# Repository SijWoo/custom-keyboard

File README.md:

# custom-keyboard
Holds the electronic pcb files and src code for my custom keyboard

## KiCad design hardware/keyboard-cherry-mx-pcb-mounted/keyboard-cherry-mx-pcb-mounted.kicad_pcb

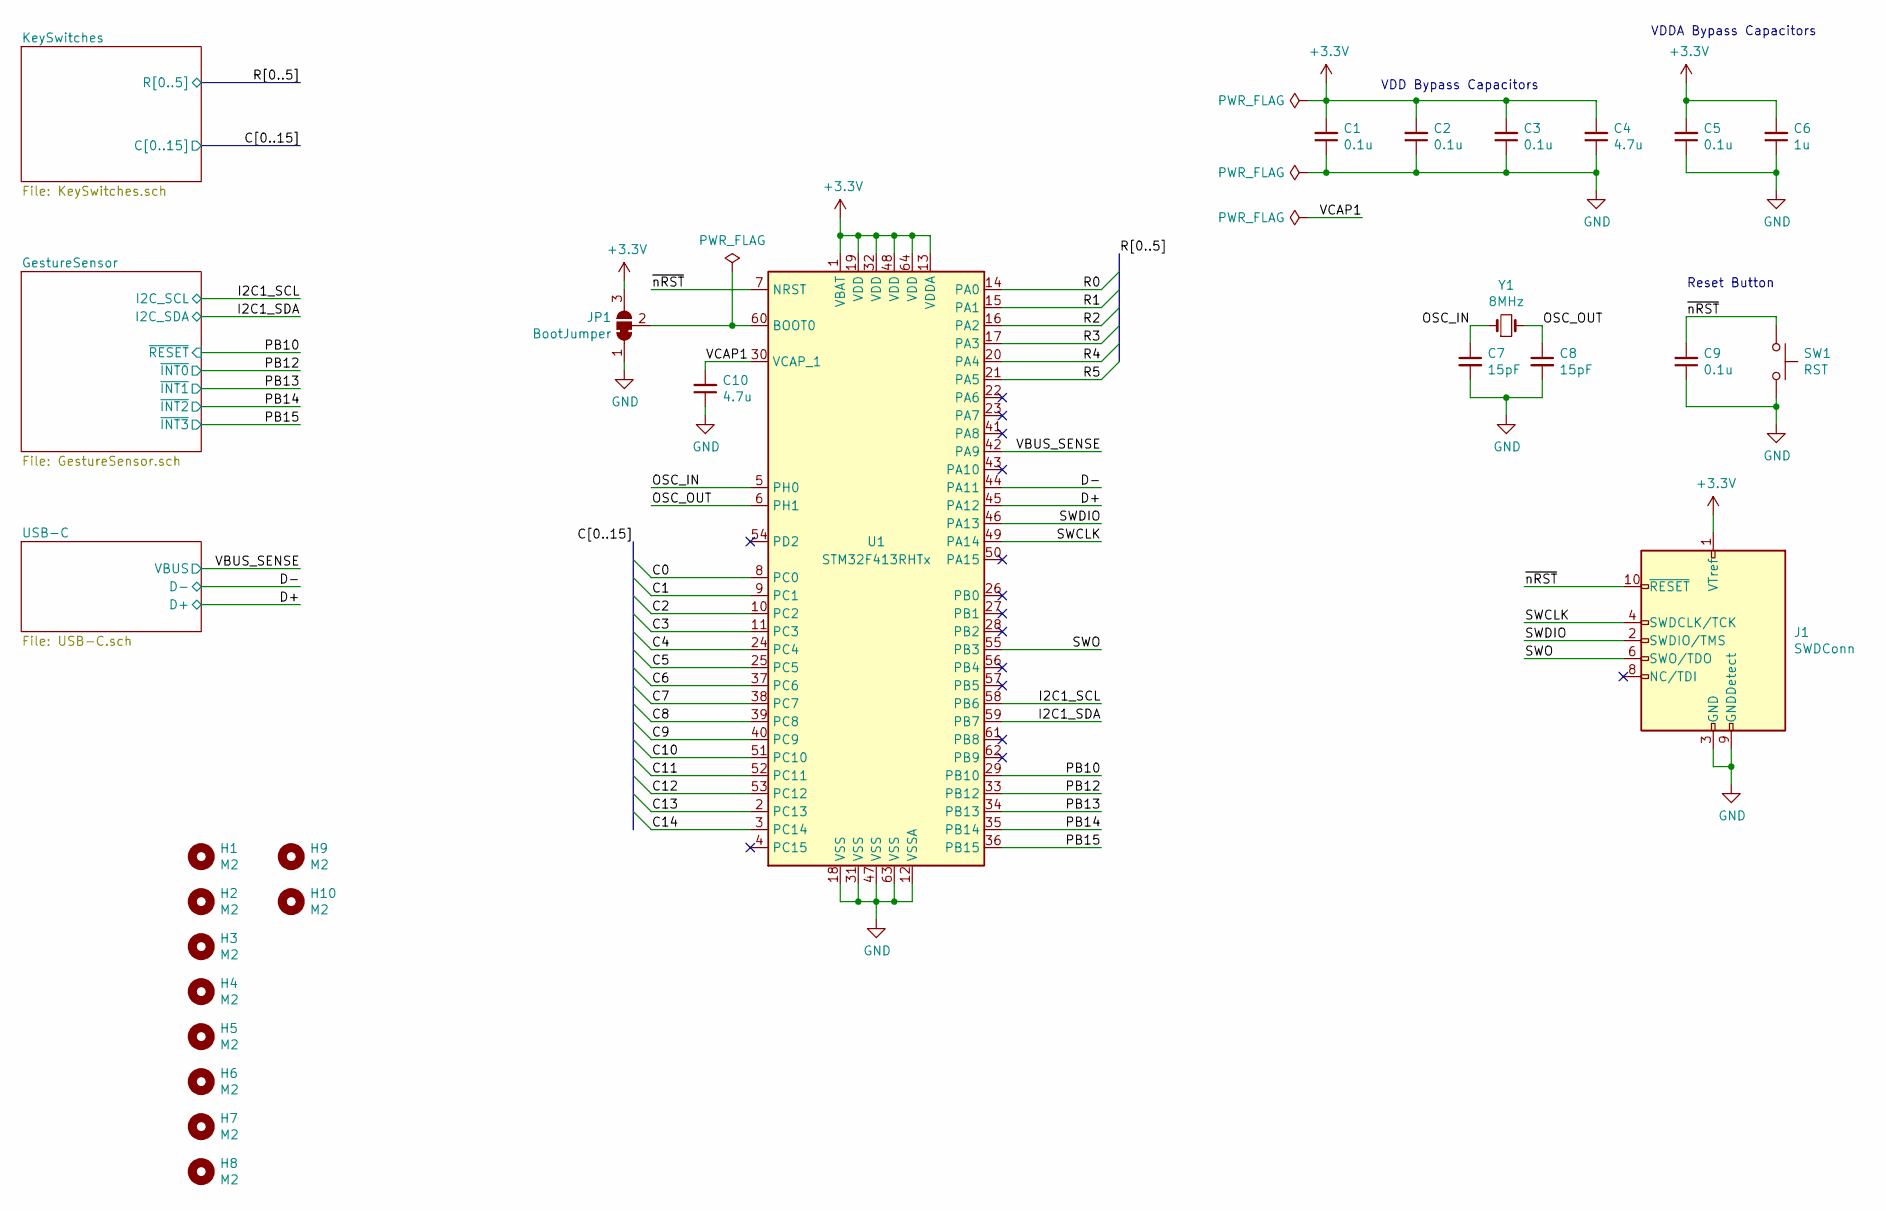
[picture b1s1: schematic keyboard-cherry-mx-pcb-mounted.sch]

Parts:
C1, C2, C3, C5: 0.1u; C_0603_1608Metric
C4, C10: 4.7u; C_0603_1608Metric
C6: 1u; C_0603_1608Metric
C7, C8: 15pF; C_0603_1608Metric
C9: 0.1u; C_0805_2012Metric
H1, H2, H3, H4, H5, H6, H7, H8, H9, H10: M2; MountingHole_2.2mm_M2
J1: SWDConn; Tag-Connect_TC2050-IDC-NL_2x05_P1.27mm_Vertical
JP1: BootJumper; SolderJumper-3_P1.3mm_Bridged12_Pad1.0x1.5mm
SW1: RST; SW_SPST_B3U-1000P
U1: STM32F413RHTx; LQFP-64_10x10mm_P0.5mm
Y1: 8MHz; Crystal_SMD_TXC_7A-2Pin_5x3.2mm

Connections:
+3V3: C1.2, C2.2, C3.2, C4.2, C5.2, C6.2, J1.1 (VTref), JP1.3 (B), U1.1 (VBAT), U1.13 (VDDA), U1.19 (VDD), U1.32 (VDD), U1.48 (VDD), U1.64 (VDD); also elsewhere on the board
+5V: U1.42 (PA9); also elsewhere on the board
/C0: U1.8 (PC0); also elsewhere on the board
/C1: U1.9 (PC1); also elsewhere on the board
/C2: U1.10 (PC2); also elsewhere on the board
/C3: U1.11 (PC3); also elsewhere on the board
/C4: U1.24 (PC4); also elsewhere on the board
/C5: U1.25 (PC5); also elsewhere on the board
/C6: U1.37 (PC6); also elsewhere on the board
/C7: U1.38 (PC7); also elsewhere on the board
/C8: U1.39 (PC8); also elsewhere on the board
/C9: U1.40 (PC9); also elsewhere on the board
/C10: U1.51 (PC10); also elsewhere on the board
/C11: U1.52 (PC11); also elsewhere on the board
/C12: U1.53 (PC12); also elsewhere on the board
/C13: U1.2 (PC13); also elsewhere on the board
/C14: U1.3 (PC14); also elsewhere on the board
/D+: U1.45 (PA12); also elsewhere on the board
/D-: U1.44 (PA11); also elsewhere on the board
/I2C1_SCL: U1.58 (PB6); also elsewhere on the board
/I2C1_SDA: U1.59 (PB7); also elsewhere on the board
/OSC_IN: C7.1, U1.5 (PH0), Y1.1
/OSC_OUT: C8.1, U1.6 (PH1), Y1.2
/PB10: U1.29 (PB10); also elsewhere on the board
/PB12: U1.33 (PB12); also elsewhere on the board
/PB13: U1.34 (PB13); also elsewhere on the board
/PB14: U1.35 (PB14); also elsewhere on the board
/PB15: U1.36 (PB15); also elsewhere on the board
/R0: U1.14 (PA0); also elsewhere on the board
/R1: U1.15 (PA1); also elsewhere on the board
/R2: U1.16 (PA2); also elsewhere on the board
/R3: U1.17 (PA3); also elsewhere on the board
/R4: U1.20 (PA4); also elsewhere on the board
/R5: U1.21 (PA5); also elsewhere on the board
/SWCLK: J1.4 (SWDCLK/TCK), U1.49 (PA14)
/SWDIO: J1.2 (SWDIO/TMS), U1.46 (PA13)
/SWO: J1.6 (SWO/TDO), U1.55 (PB3)
/VCAP1: C10.2, U1.30 (VCAP_1)
/~nRST: C9.2, J1.10 (~RESET~), SW1.1, U1.7 (NRST)
GND: C1.1, C2.1, C3.1, C4.1, C5.1, C6.1, C7.2, C8.2, C9.1, C10.1, J1.3 (GND), J1.5 (GND), J1.9 (GNDDetect), JP1.1 (A), SW1.2, U1.12 (VSSA), U1.18 (VSS), U1.31 (VSS), U1.47 (VSS), U1.63 (VSS); also elsewhere on the board
unnamed: JP1.2 (C), U1.60 (BOOT0)

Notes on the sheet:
VDDA Bypass Capacitors
Reset Button
VDD Bypass Capacitors

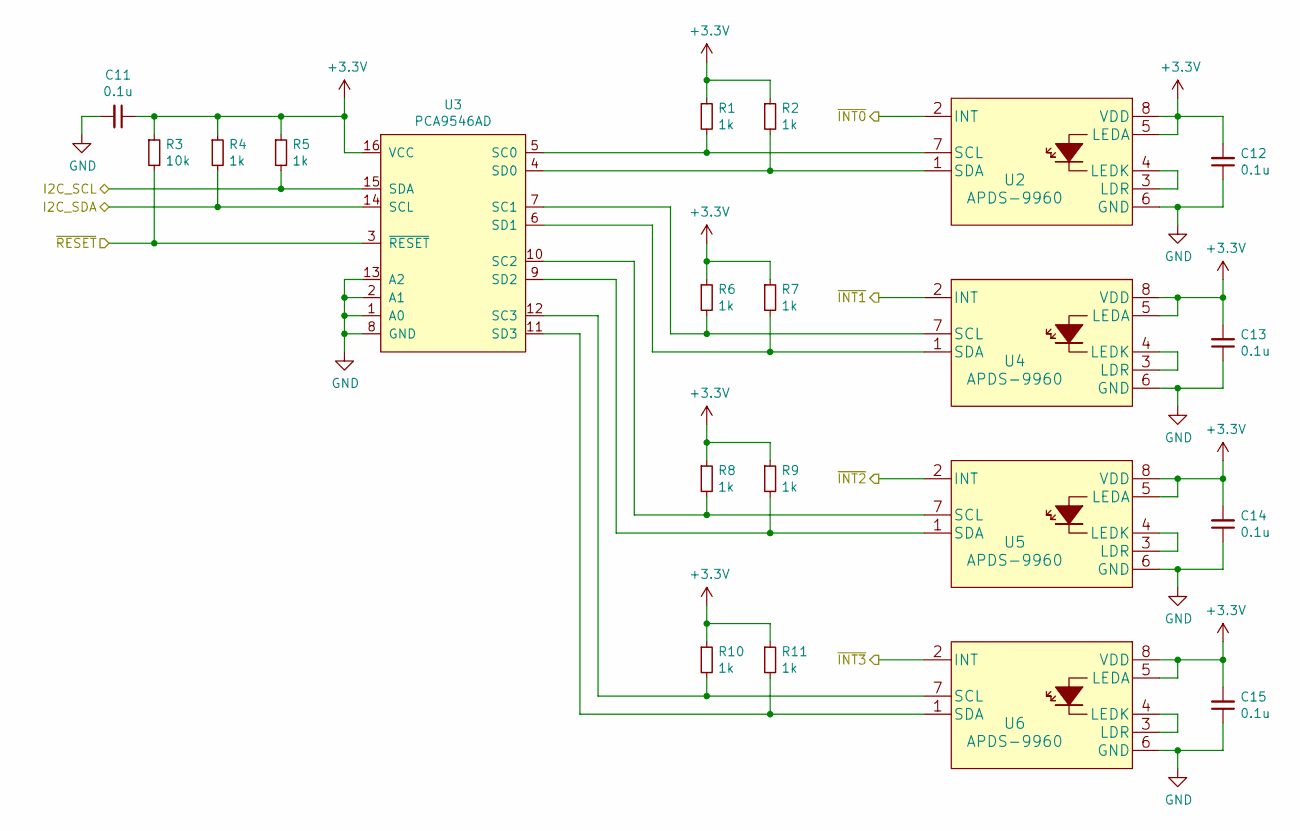
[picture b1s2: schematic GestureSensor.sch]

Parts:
C11, C12, C13, C14, C15: 0.1u; C_0805_2012Metric
R1, R2, R4, R5, R6, R7, R8, R9, R10, R11: 1k; R_0805_2012Metric
R3: 10k; R_0805_2012Metric
U2, U4, U5, U6: APDS-9960; APDS-9930
U3: PCA9546AD; SOIC-16_3.9x9.9mm_P1.27mm

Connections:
+3V3: C11.1, C12.2, C13.2, C14.2, C15.2, R1.1, R2.1, R3.1, R4.1, R5.1, R6.1, R7.1, R8.1, R9.1, R10.1, R11.1, U2.5 (LEDA), U2.8 (VDD), U3.16 (VCC), U4.5 (LEDA), U4.8 (VDD), U5.5 (LEDA), U5.8 (VDD), U6.5 (LEDA), U6.8 (VDD); also elsewhere on the board
/I2C1_SCL: R5.2, U3.15 (SDA); also elsewhere on the board
/I2C1_SDA: R4.2, U3.14 (SCL); also elsewhere on the board
/PB10: R3.2, U3.3 (~RESET); also elsewhere on the board
/PB12: U2.2 (INT); also elsewhere on the board
/PB13: U4.2 (INT); also elsewhere on the board
/PB14: U5.2 (INT); also elsewhere on the board
/PB15: U6.2 (INT); also elsewhere on the board
GND: C11.2, C12.1, C13.1, C14.1, C15.1, U2.6 (GND), U3.1 (A0), U3.2 (A1), U3.8 (GND), U3.13 (A2), U4.6 (GND), U5.6 (GND), U6.6 (GND); also elsewhere on the board
unnamed: R1.2, U2.7 (SCL), U3.5 (SC0)
unnamed: R2.2, U2.1 (SDA), U3.4 (SD0)
unnamed: R6.2, U3.7 (SC1), U4.7 (SCL)
unnamed: R7.2, U3.6 (SD1), U4.1 (SDA)
unnamed: R8.2, U3.10 (SC2), U5.7 (SCL)
unnamed: R9.2, U3.9 (SD2), U5.1 (SDA)
unnamed: R10.2, U3.12 (SC3), U6.7 (SCL)
unnamed: R11.2, U3.11 (SD3), U6.1 (SDA)
unnamed: U2.3 (LDR), U2.4 (LEDK)
unnamed: U4.3 (LDR), U4.4 (LEDK)
unnamed: U5.3 (LDR), U5.4 (LEDK)
unnamed: U6.3 (LDR), U6.4 (LEDK)

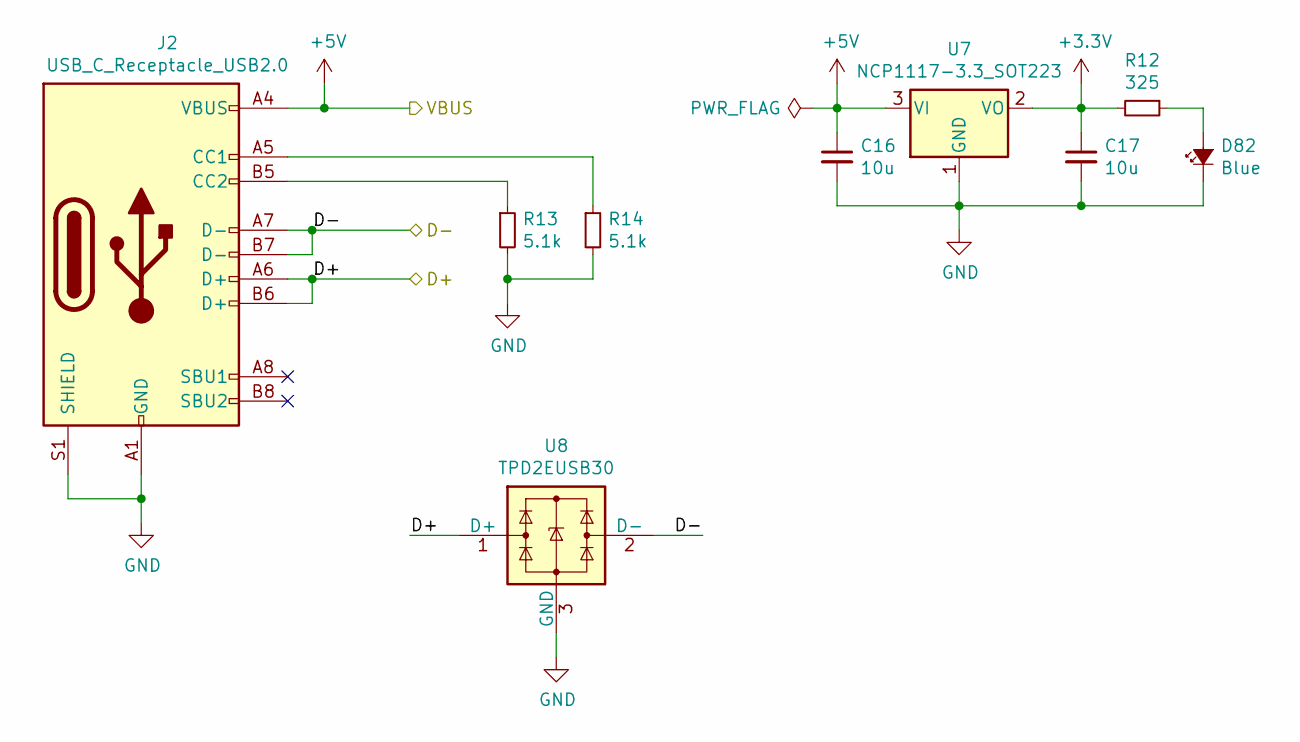
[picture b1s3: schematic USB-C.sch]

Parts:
C16, C17: 10u; C_0805_2012Metric
D82: Blue; LED_0805_2012Metric
J2: USB_C_Receptacle_USB2.0; USB_C_Receptacle_Wurth_632723100021
R12: 325; R_0805_2012Metric
R13, R14: 5.1k; R_0805_2012Metric
U7: NCP1117-3.3_SOT223; SOT-223-3_TabPin2
U8: TPD2EUSB30; Texas_DRT-3

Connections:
+3V3: C17.1, R12.2, U7.2 (VO); also elsewhere on the board
+5V: C16.1, J2.A4 (VBUS), J2.A9 (VBUS), J2.B4 (VBUS), J2.B9 (VBUS), U7.3 (VI); also elsewhere on the board
/D+: J2.A6 (D+), J2.B6 (D+), U8.1 (D+); also elsewhere on the board
/D-: J2.A7 (D-), J2.B7 (D-), U8.2 (D-); also elsewhere on the board
GND: C16.2, C17.2, D82.1 (K), J2.A1 (GND), J2.A12 (GND), J2.B1 (GND), J2.B12 (GND), J2.S1 (SHIELD), R13.2, R14.2, U7.1 (GND), U8.3 (GND); also elsewhere on the board
unnamed: D82.2 (A), R12.1
unnamed: J2.A5 (CC1), R14.1
unnamed: J2.B5 (CC2), R13.1

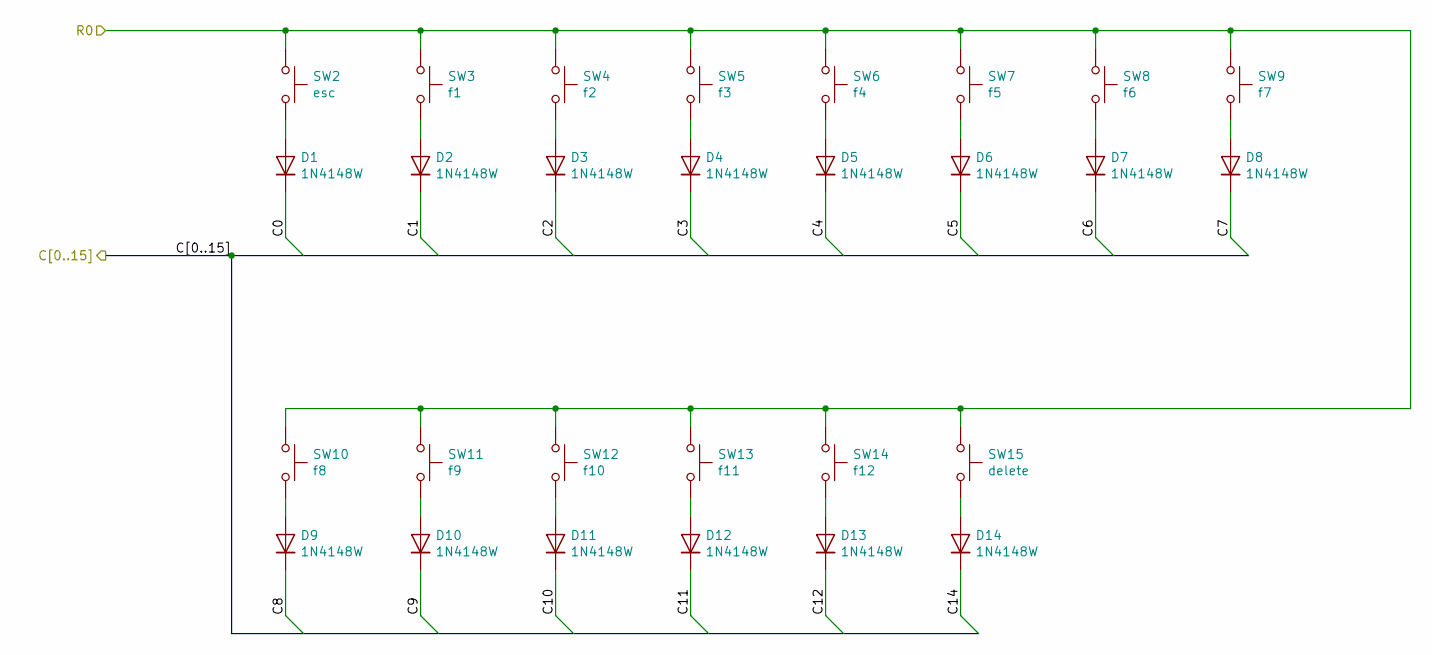
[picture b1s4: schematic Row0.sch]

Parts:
D1, D2, D3, D4, D5, D6, D7, D8, D9, D10, D11, D12, D13, D14: 1N4148W; D_SOD-123
SW2: esc; SW_Cherry_MX_1.00u_PCB
SW3: f1; SW_Cherry_MX_1.00u_PCB
SW4: f2; SW_Cherry_MX_1.00u_PCB
SW5: f3; SW_Cherry_MX_1.00u_PCB
SW6: f4; SW_Cherry_MX_1.00u_PCB
SW7: f5; SW_Cherry_MX_1.00u_PCB
SW8: f6; SW_Cherry_MX_1.00u_PCB
SW9: f7; SW_Cherry_MX_1.00u_PCB
SW10: f8; SW_Cherry_MX_1.00u_PCB
SW11: f9; SW_Cherry_MX_1.00u_PCB
SW12: f10; SW_Cherry_MX_1.00u_PCB
SW13: f11; SW_Cherry_MX_1.00u_PCB
SW14: f12; SW_Cherry_MX_1.00u_PCB
SW15: delete; SW_Cherry_MX_1.00u_PCB

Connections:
/C0: D1.1 (K); also elsewhere on the board
/C1: D2.1 (K); also elsewhere on the board
/C2: D3.1 (K); also elsewhere on the board
/C3: D4.1 (K); also elsewhere on the board
/C4: D5.1 (K); also elsewhere on the board
/C5: D6.1 (K); also elsewhere on the board
/C6: D7.1 (K); also elsewhere on the board
/C7: D8.1 (K); also elsewhere on the board
/C8: D9.1 (K); also elsewhere on the board
/C9: D10.1 (K); also elsewhere on the board
/C10: D11.1 (K); also elsewhere on the board
/C11: D12.1 (K); also elsewhere on the board
/C12: D13.1 (K); also elsewhere on the board
/C14: D14.1 (K); also elsewhere on the board
/R0: SW2.1, SW3.1, SW4.1, SW5.1, SW6.1, SW7.1, SW8.1, SW9.1, SW10.1, SW11.1, SW12.1, SW13.1, SW14.1, SW15.1; also elsewhere on the board
unnamed: D1.2 (A), SW2.2
unnamed: D2.2 (A), SW3.2
unnamed: D3.2 (A), SW4.2
unnamed: D4.2 (A), SW5.2
unnamed: D5.2 (A), SW6.2
unnamed: D6.2 (A), SW7.2
unnamed: D7.2 (A), SW8.2
unnamed: D8.2 (A), SW9.2
unnamed: D9.2 (A), SW10.2
unnamed: D10.2 (A), SW11.2
unnamed: D11.2 (A), SW12.2
unnamed: D12.2 (A), SW13.2
unnamed: D13.2 (A), SW14.2
unnamed: D14.2 (A), SW15.2

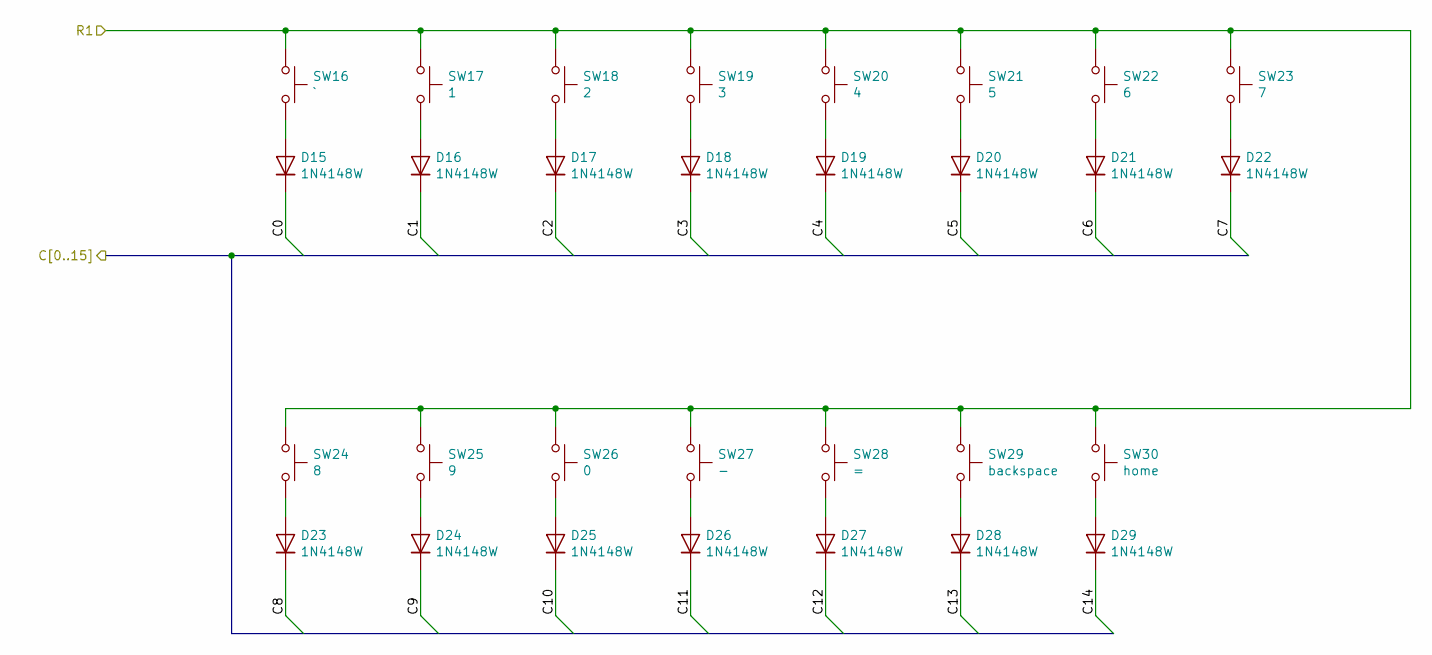
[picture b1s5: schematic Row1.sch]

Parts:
D15, D16, D17, D18, D19, D20, D21, D22, D23, D24, D25, D26, D27, D28, D29: 1N4148W; D_SOD-123
SW16: `; SW_Cherry_MX_1.00u_PCB
SW17: 1; SW_Cherry_MX_1.00u_PCB
SW18: 2; SW_Cherry_MX_1.00u_PCB
SW19: 3; SW_Cherry_MX_1.00u_PCB
SW20: 4; SW_Cherry_MX_1.00u_PCB
SW21: 5; SW_Cherry_MX_1.00u_PCB
SW22: 6; SW_Cherry_MX_1.00u_PCB
SW23: 7; SW_Cherry_MX_1.00u_PCB
SW24: 8; SW_Cherry_MX_1.00u_PCB
SW25: 9; SW_Cherry_MX_1.00u_PCB
SW26: 0; SW_Cherry_MX_1.00u_PCB
SW27: -; SW_Cherry_MX_1.00u_PCB
SW28: =; SW_Cherry_MX_1.00u_PCB
SW29: backspace; SW_Cherry_MX_2.00u_PCB
SW30: home; SW_Cherry_MX_1.00u_PCB

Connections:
/C0: D15.1 (K); also elsewhere on the board
/C1: D16.1 (K); also elsewhere on the board
/C2: D17.1 (K); also elsewhere on the board
/C3: D18.1 (K); also elsewhere on the board
/C4: D19.1 (K); also elsewhere on the board
/C5: D20.1 (K); also elsewhere on the board
/C6: D21.1 (K); also elsewhere on the board
/C7: D22.1 (K); also elsewhere on the board
/C8: D23.1 (K); also elsewhere on the board
/C9: D24.1 (K); also elsewhere on the board
/C10: D25.1 (K); also elsewhere on the board
/C11: D26.1 (K); also elsewhere on the board
/C12: D27.1 (K); also elsewhere on the board
/C13: D28.1 (K); also elsewhere on the board
/C14: D29.1 (K); also elsewhere on the board
/R1: SW16.1, SW17.1, SW18.1, SW19.1, SW20.1, SW21.1, SW22.1, SW23.1, SW24.1, SW25.1, SW26.1, SW27.1, SW28.1, SW29.1, SW30.1; also elsewhere on the board
unnamed: D15.2 (A), SW16.2
unnamed: D16.2 (A), SW17.2
unnamed: D17.2 (A), SW18.2
unnamed: D18.2 (A), SW19.2
unnamed: D19.2 (A), SW20.2
unnamed: D20.2 (A), SW21.2
unnamed: D21.2 (A), SW22.2
unnamed: D22.2 (A), SW23.2
unnamed: D23.2 (A), SW24.2
unnamed: D24.2 (A), SW25.2
unnamed: D25.2 (A), SW26.2
unnamed: D26.2 (A), SW27.2
unnamed: D27.2 (A), SW28.2
unnamed: D28.2 (A), SW29.2
unnamed: D29.2 (A), SW30.2

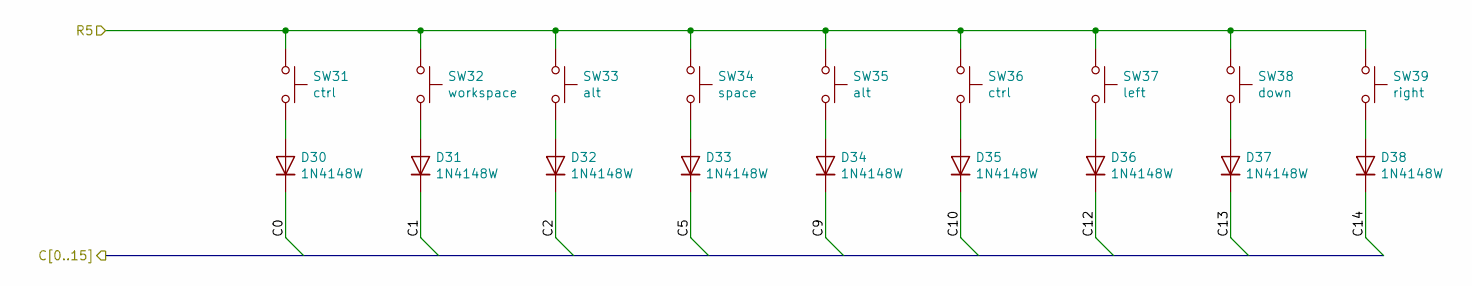
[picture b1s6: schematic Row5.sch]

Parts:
D30, D31, D32, D33, D34, D35, D36, D37, D38: 1N4148W; D_SOD-123
SW31: ctrl; SW_Cherry_MX_1.25u_PCB
SW32: workspace; SW_Cherry_MX_1.25u_PCB
SW33: alt; SW_Cherry_MX_1.25u_PCB
SW34: space; SW_Cherry_MX_6.25u_PCB
SW35: alt; SW_Cherry_MX_1.50u_PCB
SW36: ctrl; SW_Cherry_MX_1.50u_PCB
SW37: left; SW_Cherry_MX_1.00u_PCB
SW38: down; SW_Cherry_MX_1.00u_PCB
SW39: right; SW_Cherry_MX_1.00u_PCB

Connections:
/C0: D30.1 (K); also elsewhere on the board
/C1: D31.1 (K); also elsewhere on the board
/C2: D32.1 (K); also elsewhere on the board
/C5: D33.1 (K); also elsewhere on the board
/C9: D34.1 (K); also elsewhere on the board
/C10: D35.1 (K); also elsewhere on the board
/C12: D36.1 (K); also elsewhere on the board
/C13: D37.1 (K); also elsewhere on the board
/C14: D38.1 (K); also elsewhere on the board
/R5: SW31.1, SW32.1, SW33.1, SW34.1, SW35.1, SW36.1, SW37.1, SW38.1, SW39.1; also elsewhere on the board
unnamed: D30.2 (A), SW31.2
unnamed: D31.2 (A), SW32.2
unnamed: D32.2 (A), SW33.2
unnamed: D33.2 (A), SW34.2
unnamed: D34.2 (A), SW35.2
unnamed: D35.2 (A), SW36.2
unnamed: D36.2 (A), SW37.2
unnamed: D37.2 (A), SW38.2
unnamed: D38.2 (A), SW39.2

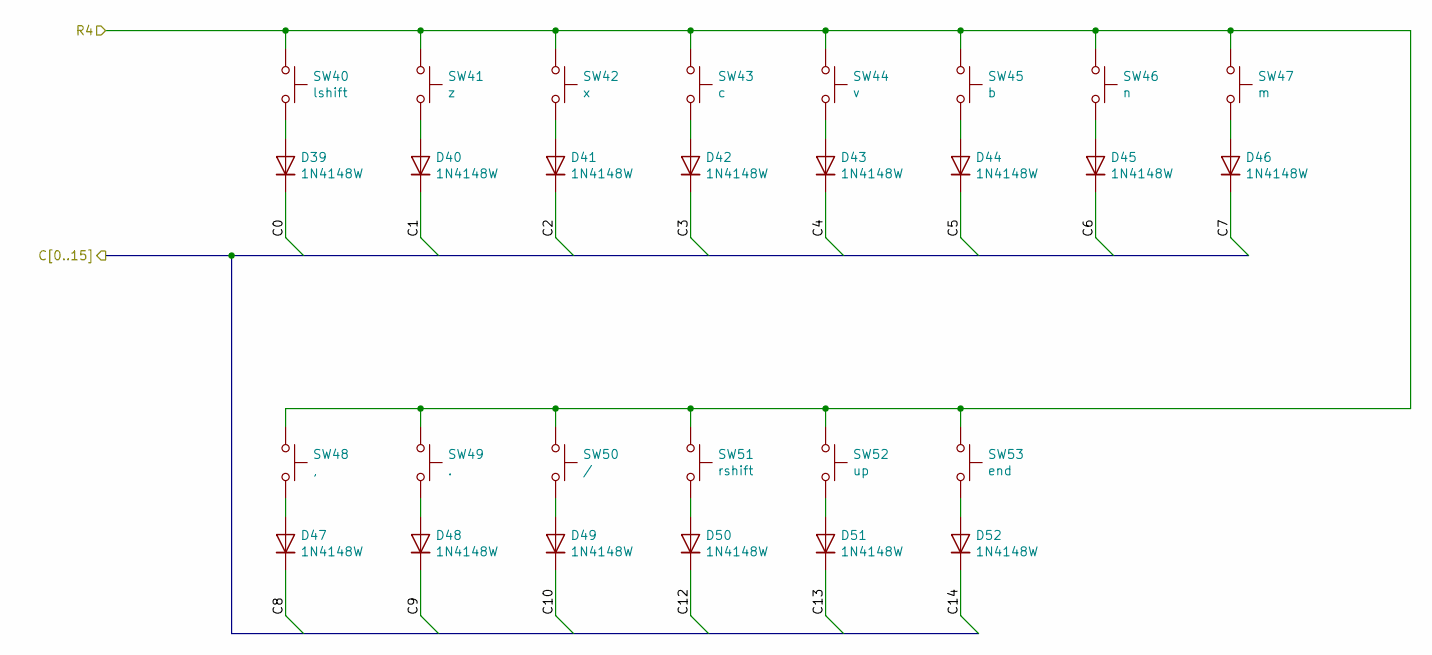
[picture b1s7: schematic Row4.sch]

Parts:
D39, D40, D41, D42, D43, D44, D45, D46, D47, D48, D49, D50, D51, D52: 1N4148W; D_SOD-123
SW40: lshift; SW_Cherry_MX_2.25u_PCB
SW41: z; SW_Cherry_MX_1.00u_PCB
SW42: x; SW_Cherry_MX_1.00u_PCB
SW43: c; SW_Cherry_MX_1.00u_PCB
SW44: v; SW_Cherry_MX_1.00u_PCB
SW45: b; SW_Cherry_MX_1.00u_PCB
SW46: n; SW_Cherry_MX_1.00u_PCB
SW47: m; SW_Cherry_MX_1.00u_PCB
SW48: ,; SW_Cherry_MX_1.00u_PCB
SW49: .; SW_Cherry_MX_1.00u_PCB
SW50: /; SW_Cherry_MX_1.00u_PCB
SW51: rshift; SW_Cherry_MX_1.75u_PCB
SW52: up; SW_Cherry_MX_1.00u_PCB
SW53: end; SW_Cherry_MX_1.00u_PCB

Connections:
/C0: D39.1 (K); also elsewhere on the board
/C1: D40.1 (K); also elsewhere on the board
/C2: D41.1 (K); also elsewhere on the board
/C3: D42.1 (K); also elsewhere on the board
/C4: D43.1 (K); also elsewhere on the board
/C5: D44.1 (K); also elsewhere on the board
/C6: D45.1 (K); also elsewhere on the board
/C7: D46.1 (K); also elsewhere on the board
/C8: D47.1 (K); also elsewhere on the board
/C9: D48.1 (K); also elsewhere on the board
/C10: D49.1 (K); also elsewhere on the board
/C12: D50.1 (K); also elsewhere on the board
/C13: D51.1 (K); also elsewhere on the board
/C14: D52.1 (K); also elsewhere on the board
/R4: SW40.1, SW41.1, SW42.1, SW43.1, SW44.1, SW45.1, SW46.1, SW47.1, SW48.1, SW49.1, SW50.1, SW51.1, SW52.1, SW53.1; also elsewhere on the board
unnamed: D39.2 (A), SW40.2
unnamed: D40.2 (A), SW41.2
unnamed: D41.2 (A), SW42.2
unnamed: D42.2 (A), SW43.2
unnamed: D43.2 (A), SW44.2
unnamed: D44.2 (A), SW45.2
unnamed: D45.2 (A), SW46.2
unnamed: D46.2 (A), SW47.2
unnamed: D47.2 (A), SW48.2
unnamed: D48.2 (A), SW49.2
unnamed: D49.2 (A), SW50.2
unnamed: D50.2 (A), SW51.2
unnamed: D51.2 (A), SW52.2
unnamed: D52.2 (A), SW53.2

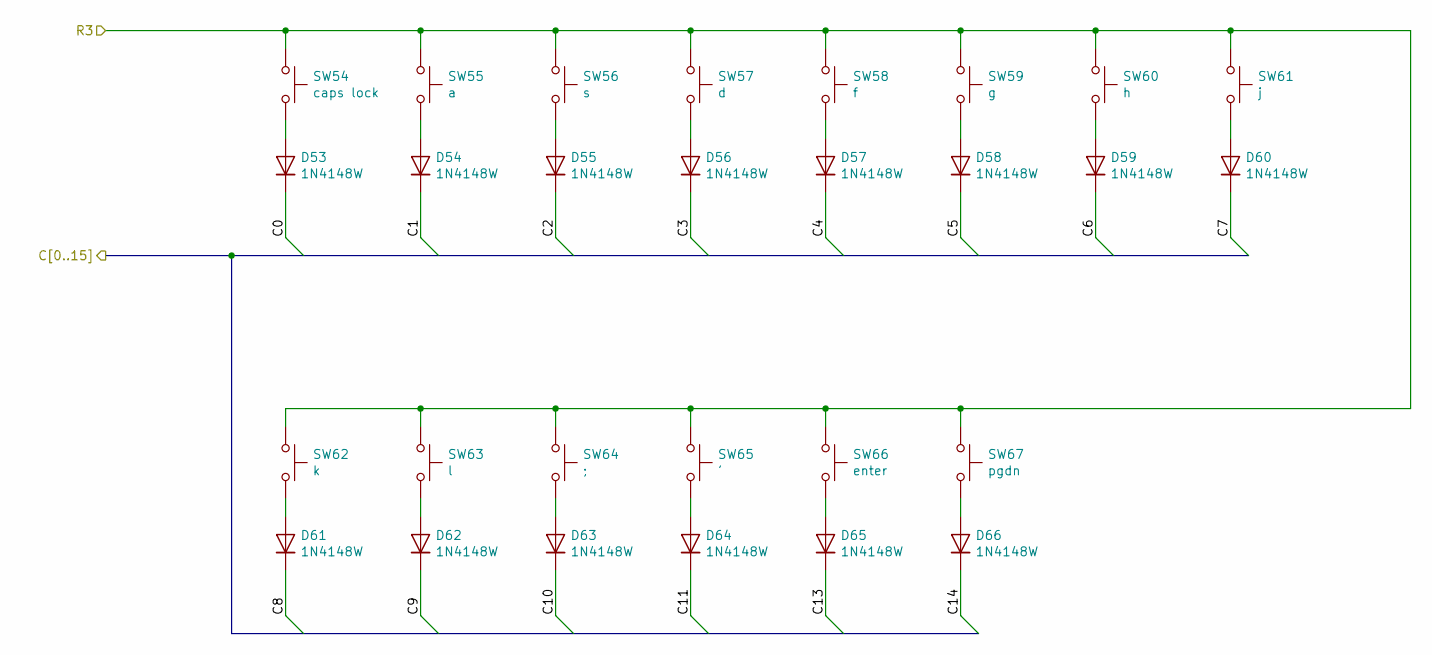
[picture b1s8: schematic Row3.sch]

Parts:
D53, D54, D55, D56, D57, D58, D59, D60, D61, D62, D63, D64, D65, D66: 1N4148W; D_SOD-123
SW54: caps lock; SW_Cherry_MX_1.75u_PCB
SW55: a; SW_Cherry_MX_1.00u_PCB
SW56: s; SW_Cherry_MX_1.00u_PCB
SW57: d; SW_Cherry_MX_1.00u_PCB
SW58: f; SW_Cherry_MX_1.00u_PCB
SW59: g; SW_Cherry_MX_1.00u_PCB
SW60: h; SW_Cherry_MX_1.00u_PCB
SW61: j; SW_Cherry_MX_1.00u_PCB
SW62: k; SW_Cherry_MX_1.00u_PCB
SW63: l; SW_Cherry_MX_1.00u_PCB
SW64: ;; SW_Cherry_MX_1.00u_PCB
SW65: '; SW_Cherry_MX_1.00u_PCB
SW66: enter; SW_Cherry_MX_2.25u_PCB
SW67: pgdn; SW_Cherry_MX_1.00u_PCB

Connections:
/C0: D53.1 (K); also elsewhere on the board
/C1: D54.1 (K); also elsewhere on the board
/C2: D55.1 (K); also elsewhere on the board
/C3: D56.1 (K); also elsewhere on the board
/C4: D57.1 (K); also elsewhere on the board
/C5: D58.1 (K); also elsewhere on the board
/C6: D59.1 (K); also elsewhere on the board
/C7: D60.1 (K); also elsewhere on the board
/C8: D61.1 (K); also elsewhere on the board
/C9: D62.1 (K); also elsewhere on the board
/C10: D63.1 (K); also elsewhere on the board
/C11: D64.1 (K); also elsewhere on the board
/C13: D65.1 (K); also elsewhere on the board
/C14: D66.1 (K); also elsewhere on the board
/R3: SW54.1, SW55.1, SW56.1, SW57.1, SW58.1, SW59.1, SW60.1, SW61.1, SW62.1, SW63.1, SW64.1, SW65.1, SW66.1, SW67.1; also elsewhere on the board
unnamed: D53.2 (A), SW54.2
unnamed: D54.2 (A), SW55.2
unnamed: D55.2 (A), SW56.2
unnamed: D56.2 (A), SW57.2
unnamed: D57.2 (A), SW58.2
unnamed: D58.2 (A), SW59.2
unnamed: D59.2 (A), SW60.2
unnamed: D60.2 (A), SW61.2
unnamed: D61.2 (A), SW62.2
unnamed: D62.2 (A), SW63.2
unnamed: D63.2 (A), SW64.2
unnamed: D64.2 (A), SW65.2
unnamed: D65.2 (A), SW66.2
unnamed: D66.2 (A), SW67.2

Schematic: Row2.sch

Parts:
D67, D68, D69, D70, D71, D72, D73, D74, D75, D76, D77, D78, D79, D80, D81: 1N4148W; D_SOD-123
SW68: tab; SW_Cherry_MX_1.50u_PCB
SW69: q; SW_Cherry_MX_1.00u_PCB
SW70: w; SW_Cherry_MX_1.00u_PCB
SW71: e; SW_Cherry_MX_1.00u_PCB
SW72: r; SW_Cherry_MX_1.00u_PCB
SW73: t; SW_Cherry_MX_1.00u_PCB
SW74: y; SW_Cherry_MX_1.00u_PCB
SW75: u; SW_Cherry_MX_1.00u_PCB
SW76: i; SW_Cherry_MX_1.00u_PCB
SW77: o; SW_Cherry_MX_1.00u_PCB
SW78: p; SW_Cherry_MX_1.00u_PCB
SW79: [; SW_Cherry_MX_1.00u_PCB
SW80: ]; SW_Cherry_MX_1.00u_PCB
SW81: \\; SW_Cherry_MX_1.50u_PCB
SW82: pgup; SW_Cherry_MX_1.00u_PCB

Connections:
/C0: D67.1 (K); also elsewhere on the board
/C1: D68.1 (K); also elsewhere on the board
/C2: D69.1 (K); also elsewhere on the board
/C3: D70.1 (K); also elsewhere on the board
/C4: D71.1 (K); also elsewhere on the board
/C5: D72.1 (K); also elsewhere on the board
/C6: D73.1 (K); also elsewhere on the board
/C7: D74.1 (K); also elsewhere on the board
/C8: D75.1 (K); also elsewhere on the board
/C9: D76.1 (K); also elsewhere on the board
/C10: D77.1 (K); also elsewhere on the board
/C11: D78.1 (K); also elsewhere on the board
/C12: D79.1 (K); also elsewhere on the board
/C13: D80.1 (K); also elsewhere on the board
/C14: D81.1 (K); also elsewhere on the board
/R2: SW68.1, SW69.1, SW70.1, SW71.1, SW72.1, SW73.1, SW74.1, SW75.1, SW76.1, SW77.1, SW78.1, SW79.1, SW80.1, SW81.1, SW82.1; also elsewhere on the board
unnamed: D67.2 (A), SW68.2
unnamed: D68.2 (A), SW69.2
unnamed: D69.2 (A), SW70.2
unnamed: D70.2 (A), SW71.2
unnamed: D71.2 (A), SW72.2
unnamed: D72.2 (A), SW73.2
unnamed: D73.2 (A), SW74.2
unnamed: D74.2 (A), SW75.2
unnamed: D75.2 (A), SW76.2
unnamed: D76.2 (A), SW77.2
unnamed: D77.2 (A), SW78.2
unnamed: D78.2 (A), SW79.2
unnamed: D79.2 (A), SW80.2
unnamed: D80.2 (A), SW81.2
unnamed: D81.2 (A), SW82.2

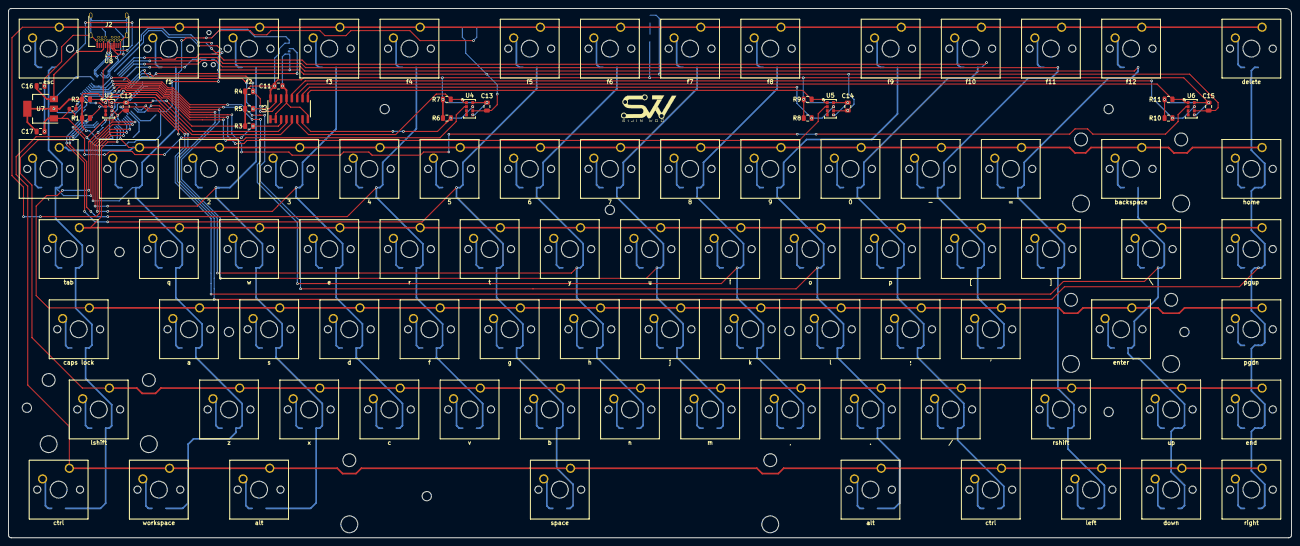
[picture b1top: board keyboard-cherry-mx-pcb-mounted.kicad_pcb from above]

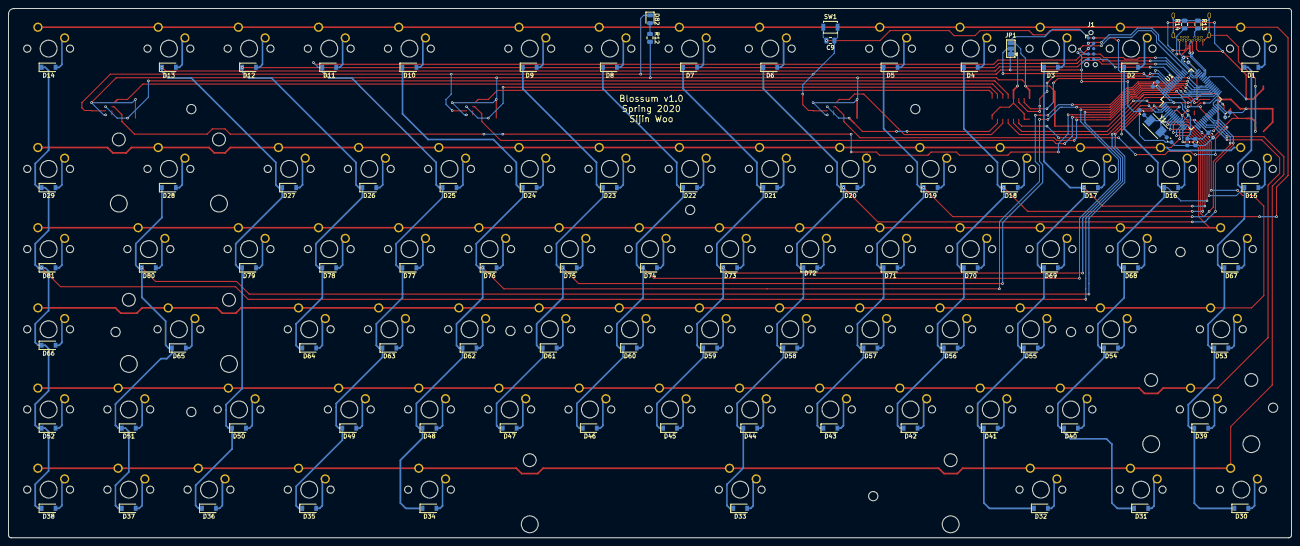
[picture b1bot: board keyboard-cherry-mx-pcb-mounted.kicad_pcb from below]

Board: 2 copper layers, 304.8 x 125.7 mm, 217 parts (99 on the bottom side), 137 nets.

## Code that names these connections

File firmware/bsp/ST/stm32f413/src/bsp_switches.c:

#include "common_types.h"
#include "stm32f4xx_ll_gpio.h"
#include "stm32f4xx_ll_bus.h"

/**
 * @brief   Initializes the GPIO interface. The Row pins need to be initializes as inputs,
 *          the Column pins should be easily modifiable to change it to an input and output.
 * @note    The Row pins should enable internal pull-up resistors.
 * @note    All column pins are automatically set to inputs.
 * @warning Not Thread Safe.
 * @param   None
 * @return  None
 */
void BSP_Switches_Init(void) {
    // TODO: Initialize GPIO pins that correspond to the rows and columns configured in keyboard_cfg.h.
    //          Rows need to have internal pull-ups enabled.
    //          Column pins should have no internal pull-up or down resistors enabled
    LL_GPIO_InitTypeDef GPIO_InitStruct = {0};

    /** Pins:
     *      Rows: [R0,R5] -> [PA0,PA5]
     *      Columns: [C0,C14] -> [PC0,PC14]
     */

    LL_AHB1_GRP1_EnableClock(LL_AHB1_GRP1_PERIPH_GPIOA);
    LL_AHB1_GRP1_EnableClock(LL_AHB1_GRP1_PERIPH_GPIOC);

    // PA pins are permanently inputs
    GPIO_InitStruct.Pin = LL_GPIO_PIN_0 | LL_GPIO_PIN_1 | LL_GPIO_PIN_2 | LL_GPIO_PIN_3 | LL_GPIO_PIN_4 | LL_GPIO_PIN_5;
    GPIO_InitStruct.Alternate = LL_GPIO_AF_0;
    GPIO_InitStruct.Mode = LL_GPIO_MODE_INPUT;
    GPIO_InitStruct.OutputType = LL_GPIO_OUTPUT_PUSHPULL;
    GPIO_InitStruct.Pull = LL_GPIO_PULL_UP;     // Internal Pull-Ups
    GPIO_InitStruct.Speed = LL_GPIO_SPEED_FREQ_MEDIUM;
    LL_GPIO_Init(GPIOA, &GPIO_InitStruct);

    // PC pins are initially set to inputs
    GPIO_InitStruct.Pin = 0xEFFF;
    GPIO_InitStruct.Pull = LL_GPIO_PULL_NO;     // No internal pull resistors
    LL_GPIO_Init(GPIOC, &GPIO_InitStruct);
}

/**
 * @brief   Sets the direction of the column pins.
 * @note    If the direction of a pin is set to an output, the data register is automatically filled with 0.
 * @warning Not Thread Safe.
 * @param   pins : mask of which pins to configure. ([0] corresponds to C0 and so on)
 * @param   dir : Direction enum. Specifies which direction the selected pins should be configued.
 * @return  None
 */
void BSP_Switches_SetColumnDirection(uint32_t pins, Direction dir) {
    // TODO: whichever bits the 'pins' variable are set to needs to be configured to whatever dir is.
    //          If the dir as an output, then the state should be set to 0.

    uint32_t mode = LL_GPIO_MODE_INPUT;

    if(dir == Output)
        mode = LL_GPIO_MODE_OUTPUT;

    for(int32_t i = 0; i <= 14; i++) {
        // If bit (1<<i) is 1, then dir should be set, otherwise leave that pin (bit) alone.
        if(pins | (1<<i)) {
            LL_GPIO_SetPinMode(GPIOC, (1<<i), mode);
        }
    }
}

/**
 * @brief   Gets what state of each row pins.
 * @warning Not Thread Safe.
 * @param   None
 * @return  Bitmap of the Row pins states
 */
uint32_t BSP_Switches_GetRowInputs(void) {
    // TODO: return the bitmap of the row input pins
    return GPIOA->IDR & 0x3F;
}

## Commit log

2020-03-10 Adds pads of cherry mx footprints and starter kicad project for custom keyboard.
2020-03-11 Adds submodule from daprice's repo.
2020-03-12 Adds switch schematics for cherry mx pcb mounted board.
2020-03-12 Adds general layout for the custom keyboard.
2020-03-16 Adds RTOS src.
2020-03-16 Adds cmsis.
2020-03-16 Adds stm32 sdk in bsp folder.
2020-03-16 Adds STM32F413 to cherry mx pcb mounted board.
2020-03-17 Adds gesture sensor interface. May change to bigger stm32 package.
2020-03-17 Adds completed sensor and power connections. Still need to add USB footprint then sch are done for version 1.0
2020-03-17 All keys except for function key row are laid out to their exact locations.
2020-03-17 Tries to space function key but doesn't seem like I did anything. Saving just in case.
2020-03-17 Adds final key caps layout of a 75 keyboard.
2020-03-17 Adds board outline for the cherry mx pcb mounted keyboard.
2020-03-17 Adds more gesture sensors to the cherry mx pcb mounted keyboard.
2020-03-17 Places diodes at respective locations on cherry mx pcb mounted keyboard.
2020-03-17 Aligns the keys so the column connections are more consistent. e.g. right most keys will have same column connection.
2020-03-17 Places gesture sensors onto board layout for cherry mx pcb mounted keyboard.
2020-03-17 Changes bypass capacitors for the stm32f413 to 0603 on the cherry mx pcb mounted keyboard. Also the sensors were not centered in between row 0 and 1 so that was fixed. Y position not 2.6375in
2020-03-17 Places all components onto the board for the cherry mx pcb mounted keyboard.
2020-03-17 Starts routing all traces for the cherry mx pcb mounted keyboard.
2020-03-18 Places traces at optimal location. Need to wire up the rest of the columns.
2020-03-18 Finishes tracing for cherry mx pcb mounted keyboard.
2020-03-18 Adds cfg directory to store cfg for rtos and application.
2020-03-20 Adds mounting holes to the cherry mx pcb mounted keyboard.
2020-03-20 Moves around bsp files to make firmware portable.
2020-03-20 Adds starter code for usb and fs applications.
2020-03-20 Adds vscode config files.
2020-03-20 Adds makefile. I decided to make the code portable after I get the stm32f413 version working. Taking too much time setting it up.
2020-03-20 Adds include paths in the makefile.
2020-03-21 makefile now compiles code with rtos and stm32 hal.
2020-03-22 Reformats rtos based off of rtos-templates repo.
2020-03-22 Renames usb bsp for stm32f4
2020-03-22 Adds P/N for crystal in cherry mx pcb mounted keyboard.
2020-03-22 Deletes usbd drv files in bsp.
2020-03-22 Cleans up rtos code.
2020-03-22 Deletes audio bsp.
2020-03-22 Moves usbd_drivers to the bsp folder.
2020-03-23 Adds initial top level cmakelists.txt
2020-03-23 Removes submodule.
2020-03-23 Changes #include paths for some files. Changes from #include <Source/header.h> to #include <header.h>
2020-03-23 Deletes build file.
2020-03-23 Fixes #include for usb drivers.
2020-03-23 Fixes common src include paths and changes kal to ucos-III
2020-03-23 Edits makefile assembly paths and deletes lib_mem.c beccause there was an optimized assembly version of mem_copy
2020-03-23 Deletes cache related functionality.
2020-03-24 Adds labels for each key and creates gerber files.
2020-03-25 Compresses gerber files.
2020-03-25 Configures bsp and cfg to use STM32F4.
2020-03-25 Changes app_usbd.c to use stm32f4 bsp.
2020-03-25 Adds hid task priorities and stack sizes.
2020-03-25 Configures protocol to be keyboard for hid.
2020-03-26 Deletes unnecesarry cfg files such as fs and crc.
2020-03-28 Deletes errenuous bsp/inc folder and renames StMicroelectronics to ST
2020-03-29 Adds starter code for the drivers and apps.
2020-03-30 Moves the rtos drivers to the top of the firmware directory. COnfigures makefile to compile with modified project structure.
2020-03-30 Designs Switches driver code.
2020-03-30 Adds keyboard_cfg to easily modify the layout. Adds Gesture_Init prototype.
2020-03-30 Adds BSP switches prototypes.
2020-03-30 Completes bsp_switches code.
2020-03-30 Adds keyboard format array. Need to figure out scancodes for each key.
2020-04-01 Changes LED for power to orange on cherry mx pcb mounted keyboard.

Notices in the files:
parts and their libraries:
Copyright 2016 Accelerated Designs. All rights reserved.
